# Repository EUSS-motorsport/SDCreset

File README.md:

# SDCreset
Shutdown Circuit reset board

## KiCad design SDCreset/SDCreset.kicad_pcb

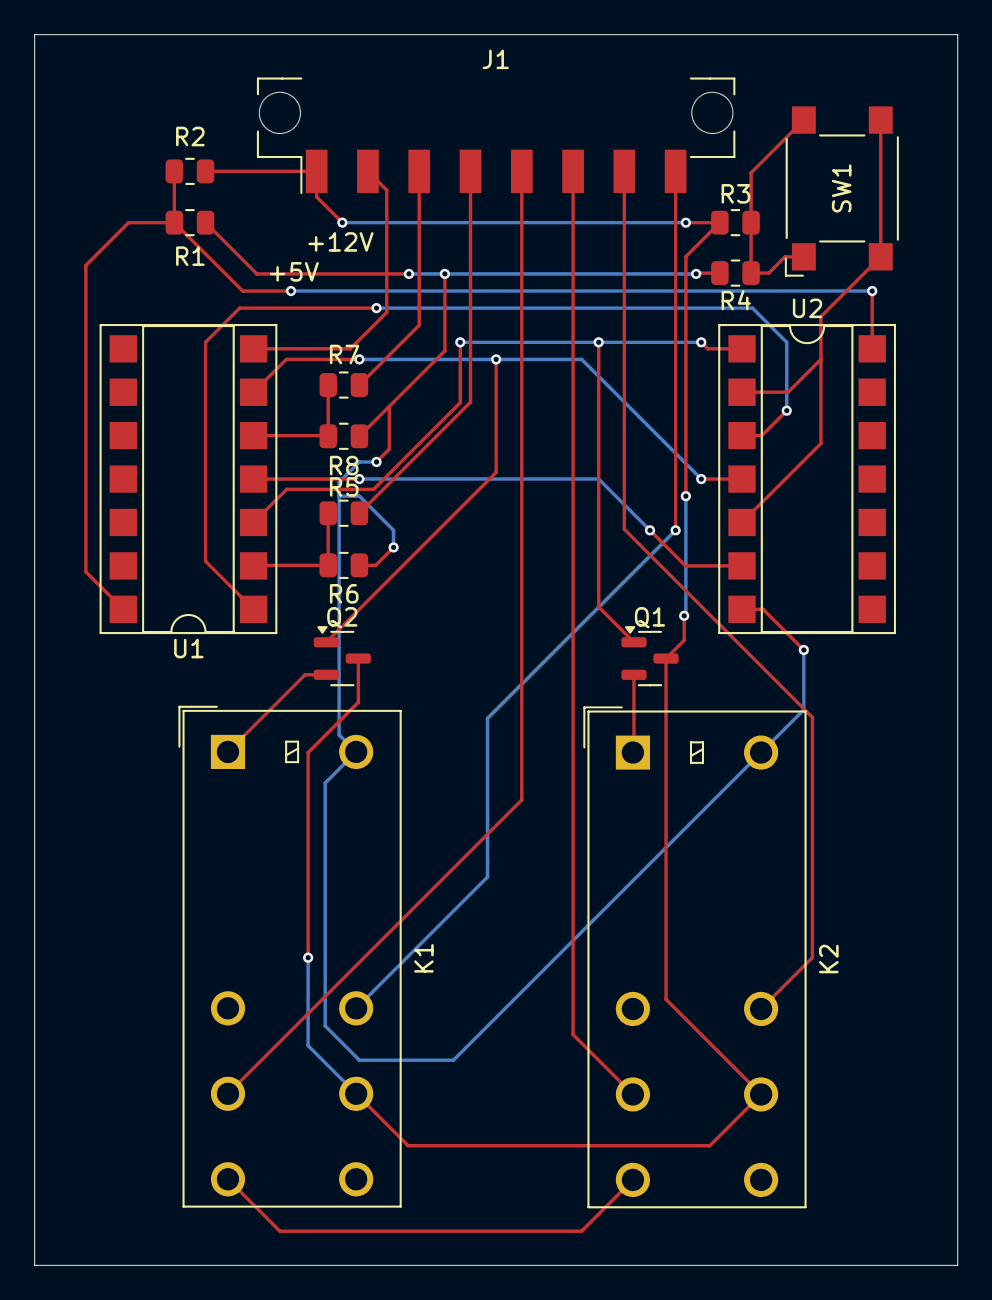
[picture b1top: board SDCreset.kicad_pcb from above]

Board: 2 copper layers, 54.0 x 72.0 mm, 16 parts (0 on the bottom side), 20 nets.

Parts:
J1: Conn_01x08_Socket; Molex_Micro-Fit_3.0_43650-0821_1x08_P3.00mm_Vertical
K1, K2: G2RL-2; Relay_DPDT_Omron_G2RL-2
Q1, Q2: BC817; SOT-23
R1, R4, R6, R8: 10k; R_0805_2012Metric
R2, R3, R5, R7: 14k; R_0805_2012Metric
SW1: SW_Omron_B3FS; SW_SPST_Omron_B3FS-105xP
U1: 74LS08; DIP-14_W7.62mm_SMDSocket_SmallPads
U2: 74LS32; DIP-14_W7.62mm_SMDSocket_SmallPads

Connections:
+12V: J1.1, K1.21, K2.21, Q1.3 (C), Q2.3 (C), R2.1, R3.1
BMS error: J1.4, R5.1
BMS led: J1.7, K2.22
BMS state: Q1.1 (B), U1.3, U2.1
GND: J1.2, K1.A2, K2.A2, R1.2, R4.2, R6.2, R8.2, U1.7 (GND), U2.7 (GND)
IMD error: J1.3, R7.1
IMD led: J1.8, K1.22
IMD state: Q2.1 (B), U1.6, U2.4
unnamed: K1.14, K2.14
unnamed: K1.A1, Q2.2 (E)
unnamed: K2.A1, Q1.2 (E)
unnamed: R5.2, R6.1, U1.2
unnamed: R7.2, R8.1, U1.5
unnamed: R3.2, R4.1, SW1.1
unnamed: SW1.2, U2.2, U2.5
unnamed: U1.1, U2.3
unnamed: U1.4, U2.6
unnamed: R1.1, R2.2, U1.14 (VCC), U2.14 (VCC)
SDC in: J1.6, K2.11
SDC out: J1.5, K1.11
